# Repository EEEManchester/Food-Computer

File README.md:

# Food-Computer
A project to create a controlled indoor growing environment using embedded systems, sensors and control

Our plan is to build a www.eee.manchester.ac.uk  prototype version of the MIT OpenAgri "Food Computer" with an idea to scaling the design out in the future. 

####Please see our Github Wiki for all information on the project

Code and hardware are forked from https://github.com/OpenAgInitiative

For more information see here
https://www.media.mit.edu/special/groups/open-ag

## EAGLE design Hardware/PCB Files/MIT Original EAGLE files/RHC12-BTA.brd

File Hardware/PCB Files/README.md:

# gro-PCB
Robusto board, RHC12, and RHC12-BTA schematics/pcbs

Robusto is split into two parts, Part1 and Part2.  RHC12 is the base connector that works with Grove and 0.1" spaced header, RHC12-BTA is for a BTA connector.  

##THESE PCBS HAVE BEEN CONVERTED TO ALTIUM DESIGNER BY EEE MANCHESTER FROM EAGLE BOARD FILES CREATED AT MIT

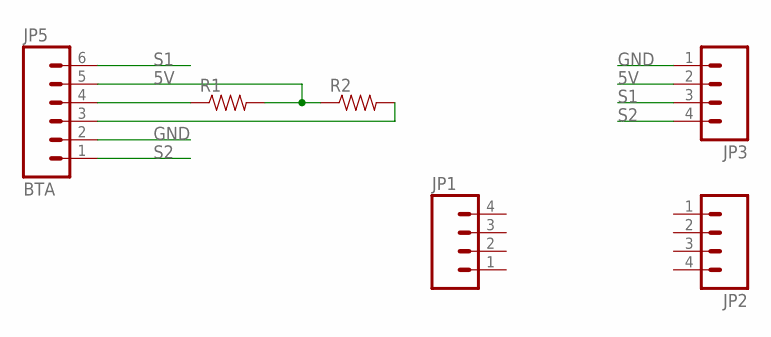
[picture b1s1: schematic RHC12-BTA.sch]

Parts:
JP1, JP2, JP3: M04NO_SILK_ALL_ROUND; 1X04_NO_SILK_ALL_ROUND
JP5: BTA
R1, R2: RESISTORPTH-1/4W; AXIAL-0.4

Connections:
5V: JP3.2, JP5.5, R1.P$2 (2), R2.P$1 (1)
GND: JP3.1, JP5.2
unnamed: JP5.4, R1.P$1 (1)
unnamed: JP5.3, R2.P$2 (2)
S1: JP3.3, JP5.6
S2: JP3.4, JP5.1

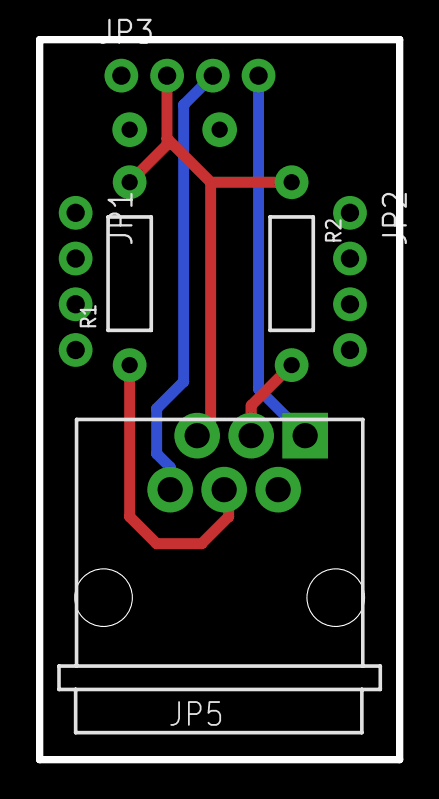
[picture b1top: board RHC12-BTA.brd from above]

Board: 2 copper layers, 20.0 x 40.0 mm, 6 parts (0 on the bottom side), 6 nets.

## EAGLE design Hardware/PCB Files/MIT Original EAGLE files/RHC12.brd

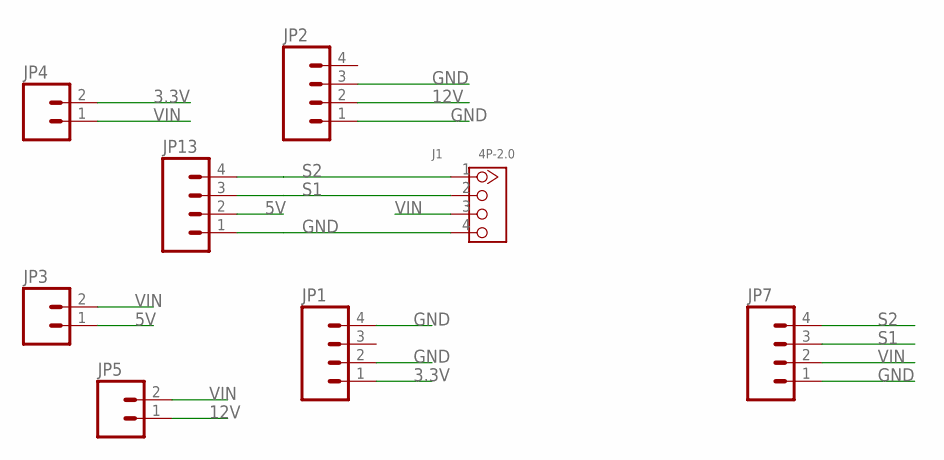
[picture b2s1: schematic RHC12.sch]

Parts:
J1: 4P-2.0; HW4-2.0
JP1, JP2, JP13: M04NO_SILK_ALL_ROUND; 1X04_NO_SILK_ALL_ROUND
JP3, JP4, JP5: M02PTH; 1X02
JP7: M04PTH; 1X04

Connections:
3.3V: JP1.1, JP4.2
5V: JP3.1, JP13.2
12V: JP2.2, JP5.1
GND: J1.4, JP1.2, JP1.4, JP2.1, JP2.3, JP7.1, JP13.1
S1: J1.2, JP7.3, JP13.3
S2: J1.1, JP7.4, JP13.4
VIN: J1.3, JP3.2, JP4.1, JP5.2, JP7.2

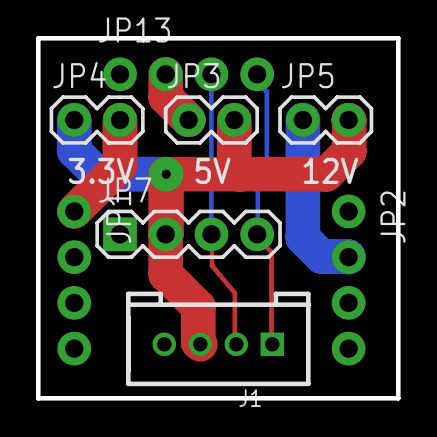
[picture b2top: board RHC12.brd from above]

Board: 2 copper layers, 20.0 x 20.0 mm, 8 parts (0 on the bottom side), 7 nets.

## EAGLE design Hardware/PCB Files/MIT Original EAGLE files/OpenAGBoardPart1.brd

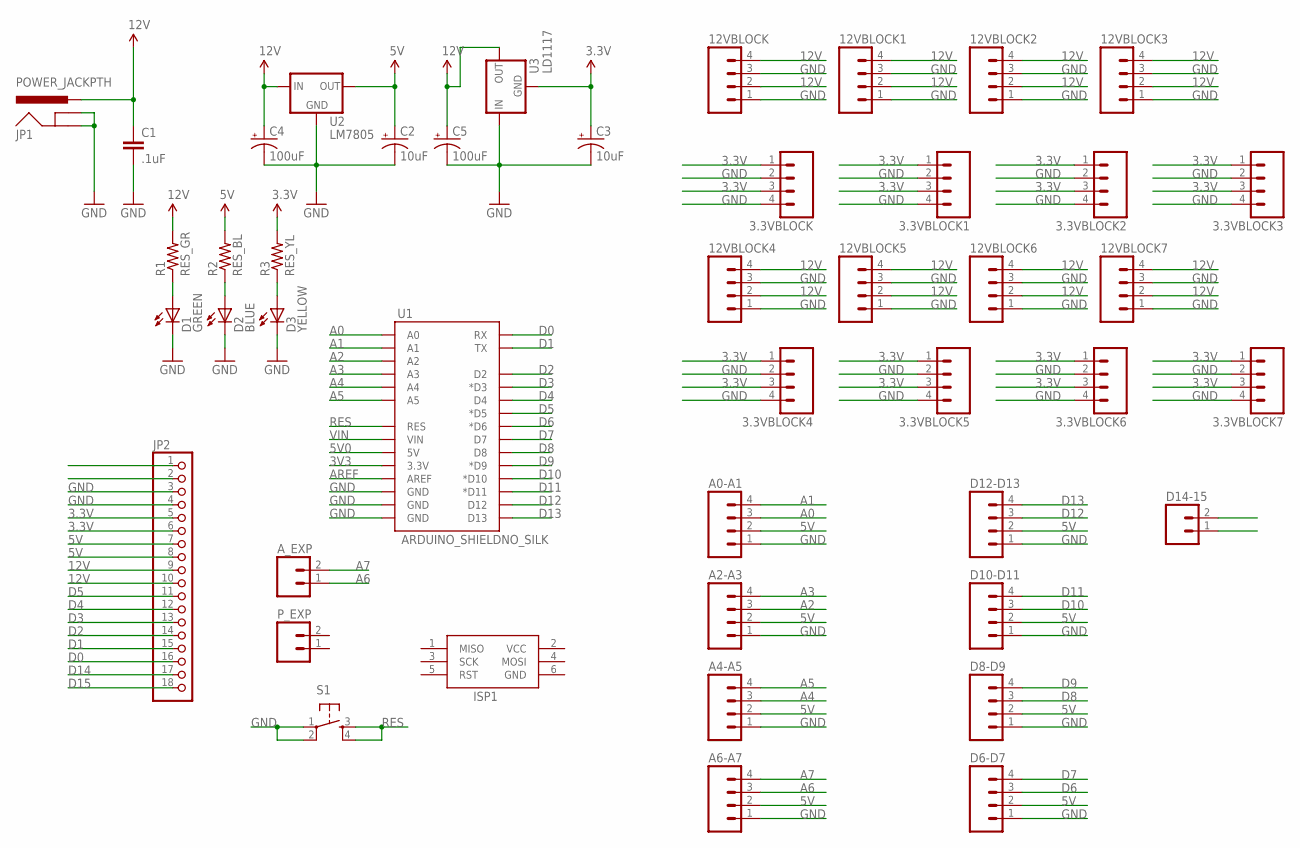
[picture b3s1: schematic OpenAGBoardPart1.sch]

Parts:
3.3VBLOCK, 3.3VBLOCK1, 3.3VBLOCK2, 3.3VBLOCK3, 3.3VBLOCK4, 3.3VBLOCK5, 3.3VBLOCK6, 3.3VBLOCK7, 12VBLOCK, 12VBLOCK1, 12VBLOCK2, 12VBLOCK3, 12VBLOCK4, 12VBLOCK5, 12VBLOCK6, 12VBLOCK7: M04NO_SILK_ALL_ROUND; 1X04_NO_SILK_ALL_ROUND
A0-A1, A2-A3, A4-A5, A6-A7: M04NO_SILK_ALL_ROUND; 1X04_NO_SILK_ALL_ROUND
A_EXP: M02PTH; 1X02
C1: .1uF; CAP-PTH-SMALL
C2, C3: 10uF; CPOL-RADIAL-10UF-25V
C4, C5: 100uF; CPOL-RADIAL-100UF-25V
D1: GREEN; LED5MM
D2: BLUE; LED5MM
D3: YELLOW; LED5MM
D6-D7, D8-D9, D10-D11, D12-D13: M04NO_SILK_ALL_ROUND; 1X04_NO_SILK_ALL_ROUND
D14-15: M02PTH; 1X02
ISP1: AVRISP-6; AVRISP
JP1: POWER_JACKPTH; POWER_JACK_PTH
JP2: PINHD-1X18-BIG; 1X18-BIG
P_EXP: M02PTH; 1X02
R1: RES_GR; AXIAL-0.4
R2: RES_BL; AXIAL-0.4
R3: RES_YL; AXIAL-0.4
S1: TAC_SWITCHPTH; TACTILE-PTH
U1: ARDUINO_SHIELDNO_SILK; DUEMILANOVE_VIAS
U2: LM7805; TO220-IGO
U3: LD1117; TO220-IGO

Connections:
3.3V: 3.3VBLOCK.1, 3.3VBLOCK.3, 3.3VBLOCK1.1, 3.3VBLOCK1.3, 3.3VBLOCK2.1, 3.3VBLOCK2.3, 3.3VBLOCK3.1, 3.3VBLOCK3.3, 3.3VBLOCK4.1, 3.3VBLOCK4.3, 3.3VBLOCK5.1, 3.3VBLOCK5.3, 3.3VBLOCK6.1, 3.3VBLOCK6.3, 3.3VBLOCK7.1, 3.3VBLOCK7.3, C3.1 (+), JP2.5, JP2.6, R3.P$2 (2), U3.GND
3V3: U1.3.3V
5V: A0-A1.2, A2-A3.2, A4-A5.2, A6-A7.2, C2.1 (+), D6-D7.2, D8-D9.2, D10-D11.2, D12-D13.2, JP2.7, JP2.8, R2.P$2 (2), U2.OUT
5V0: U1.5V
12V: 12VBLOCK.2, 12VBLOCK.4, 12VBLOCK1.2, 12VBLOCK1.4, 12VBLOCK2.2, 12VBLOCK2.4, 12VBLOCK3.2, 12VBLOCK3.4, 12VBLOCK4.2, 12VBLOCK4.4, 12VBLOCK5.2, 12VBLOCK5.4, 12VBLOCK6.2, 12VBLOCK6.4, 12VBLOCK7.2, 12VBLOCK7.4, C1.1, C4.1 (+), C5.1 (+), JP1.PWR, JP2.9, JP2.10, R1.P$2 (2), U2.IN, U3.OUT
A0: A0-A1.3, U1.A0
A1: A0-A1.4, U1.A1
A2: A2-A3.3, U1.A2
A3: A2-A3.4, U1.A3
A4: A4-A5.3, U1.A4
A5: A4-A5.4, U1.A5
A6: A6-A7.3, A_EXP.1
A7: A6-A7.4, A_EXP.2
AREF: U1.AREF
CONTINUITY_STRIP: JP2.1
D0: JP2.16, U1.RX
D1: JP2.15, U1.TX
D2: JP2.14, U1.D2
D3: JP2.13, U1.D3 (*D3)
D4: JP2.12, U1.D4
D5: JP2.11, U1.D5 (*D5)
D6: D6-D7.3, U1.D6 (*D6)
D7: D6-D7.4, U1.D7
D8: D8-D9.3, U1.D8
D9: D8-D9.4, U1.D9 (*D9)
D10: D10-D11.3, U1.D10 (*D10)
D11: D10-D11.4, U1.D11 (*D11)
D12: D12-D13.3, U1.D12
D13: D12-D13.4, U1.D13
D14: D14-15.1, JP2.17
D15: D14-15.2, JP2.18
GND: 3.3VBLOCK.2, 3.3VBLOCK.4, 3.3VBLOCK1.2, 3.3VBLOCK1.4, 3.3VBLOCK2.2, 3.3VBLOCK2.4, 3.3VBLOCK3.2, 3.3VBLOCK3.4, 3.3VBLOCK4.2, 3.3VBLOCK4.4, 3.3VBLOCK5.2, 3.3VBLOCK5.4, 3.3VBLOCK6.2, 3.3VBLOCK6.4, 3.3VBLOCK7.2, 3.3VBLOCK7.4, 12VBLOCK.1, 12VBLOCK.3, 12VBLOCK1.1, 12VBLOCK1.3, 12VBLOCK2.1, 12VBLOCK2.3, 12VBLOCK3.1, 12VBLOCK3.3, 12VBLOCK4.1, 12VBLOCK4.3, 12VBLOCK5.1, 12VBLOCK5.3, 12VBLOCK6.1, 12VBLOCK6.3, 12VBLOCK7.1, 12VBLOCK7.3, A0-A1.1, A2-A3.1, A4-A5.1, A6-A7.1, C1.2, C2.2 (-), C3.2 (-), C4.2 (-), C5.2 (-), D1.K (C), D2.K (C), D3.K (C), D6-D7.1, D8-D9.1, D10-D11.1, D12-D13.1, ISP1.6 (GND), JP1.GND, JP1.GNDBREAK, JP2.3, JP2.4, S1.1, S1.2, U1.GND@0 (GND), U1.GND@1 (GND), U1.GND@2 (GND), U2.GND, U3.IN
unnamed: D1.A, R1.P$1 (1)
unnamed: D2.A, R2.P$1 (1)
unnamed: D3.A, R3.P$1 (1)
RES: S1.3, S1.4, U1.RES
VCC: ISP1.2 (VCC)
VIN: U1.VIN

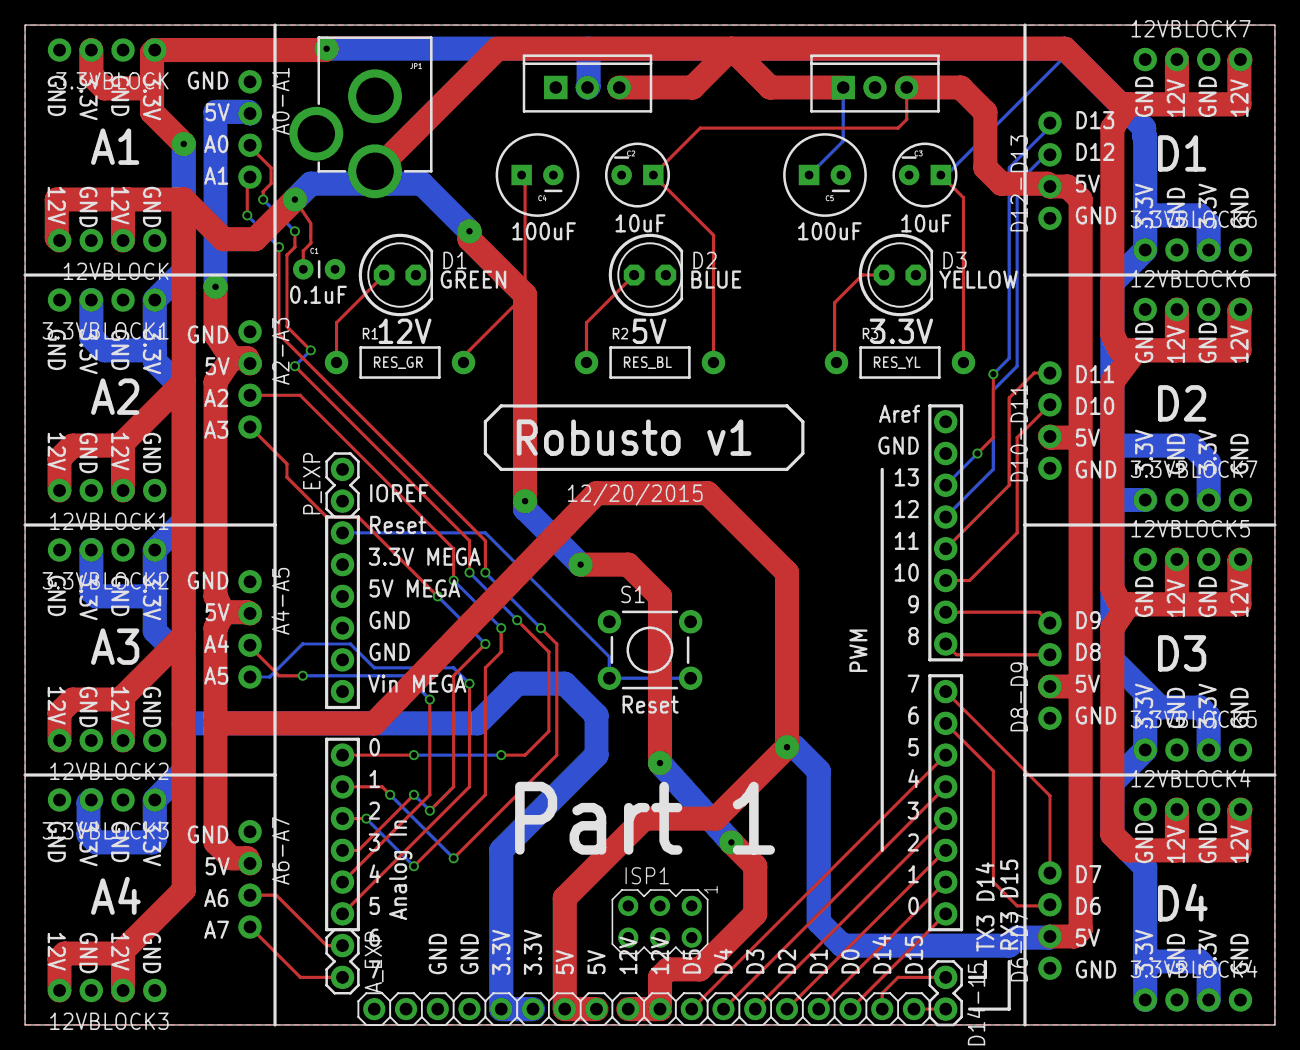
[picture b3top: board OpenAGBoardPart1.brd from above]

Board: 2 copper layers, 100.0 x 80.0 mm, 45 parts (0 on the bottom side), 32 nets.

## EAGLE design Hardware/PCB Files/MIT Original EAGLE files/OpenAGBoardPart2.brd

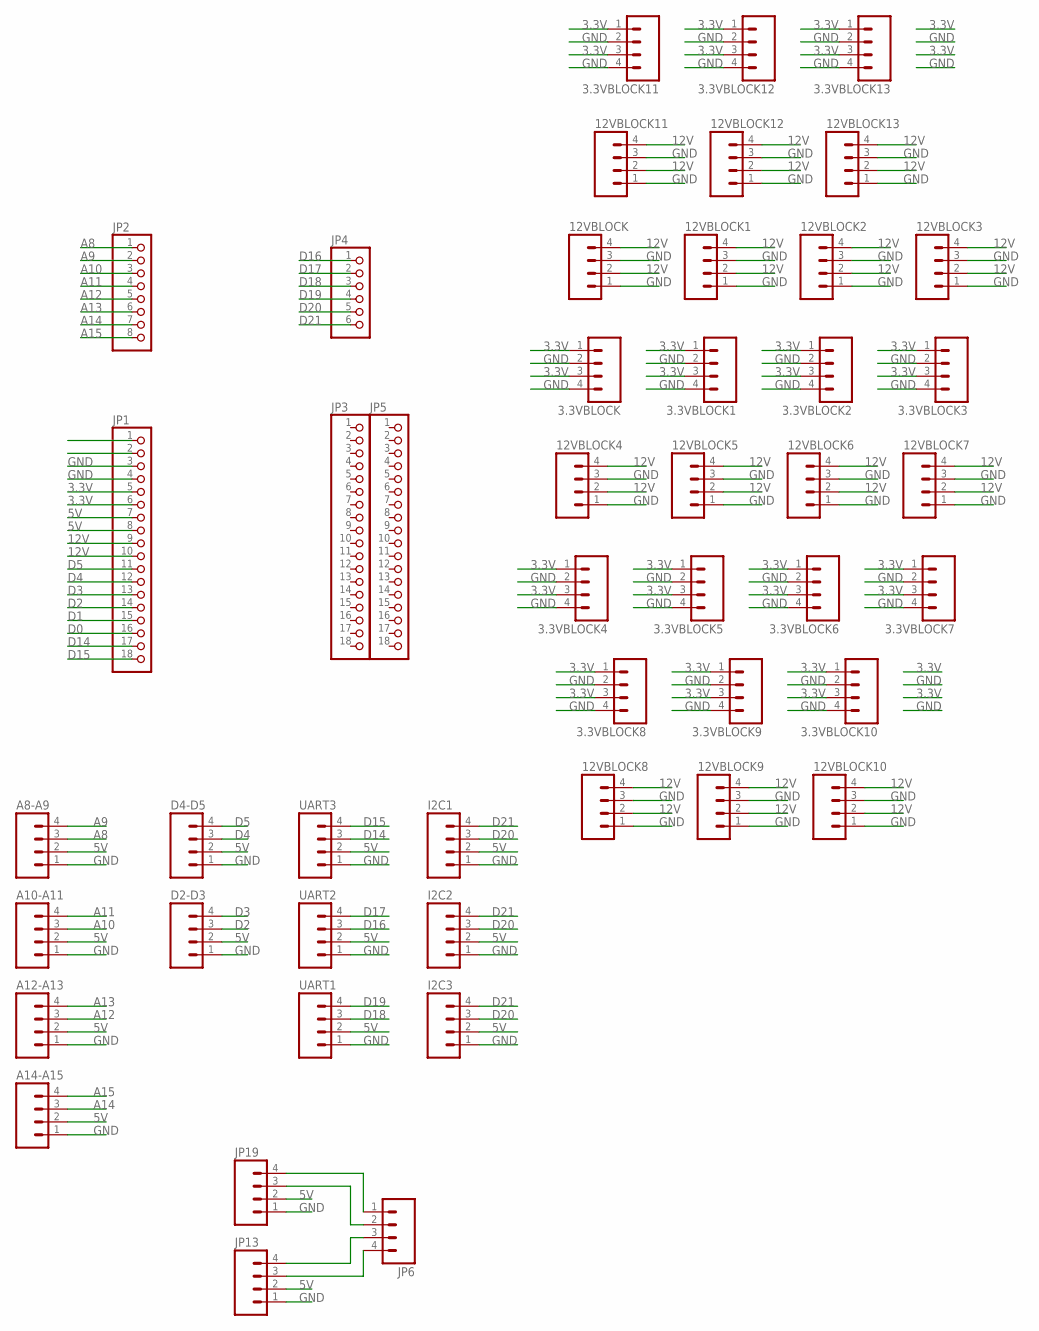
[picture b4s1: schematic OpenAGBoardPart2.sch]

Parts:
3.3VBLOCK, 3.3VBLOCK1, 3.3VBLOCK2, 3.3VBLOCK3, 3.3VBLOCK4, 3.3VBLOCK5, 3.3VBLOCK6, 3.3VBLOCK7, 3.3VBLOCK8, 3.3VBLOCK9, 3.3VBLOCK10, 3.3VBLOCK11, 3.3VBLOCK12, 3.3VBLOCK13, 12VBLOCK, 12VBLOCK1, 12VBLOCK2, 12VBLOCK3, 12VBLOCK4, 12VBLOCK5, 12VBLOCK6, 12VBLOCK7, 12VBLOCK8, 12VBLOCK9, 12VBLOCK10, 12VBLOCK11, 12VBLOCK12, 12VBLOCK13: M04NO_SILK_ALL_ROUND; 1X04_NO_SILK_ALL_ROUND
A8-A9, A10-A11, A12-A13, A14-A15: M04NO_SILK_ALL_ROUND; 1X04_NO_SILK_ALL_ROUND
D2-D3, D4-D5: M04NO_SILK_ALL_ROUND; 1X04_NO_SILK_ALL_ROUND
I2C1, I2C2, I2C3: M04NO_SILK_ALL_ROUND; 1X04_NO_SILK_ALL_ROUND
JP1, JP3, JP5: PINHD-1X18-BIG; 1X18-BIG
JP2: PINHD-1X8BIG; 1X08-BIG
JP4: PINHD-1X6B; 1X06-BIG
JP6: M04PTH; 1X04
JP13, JP19: M04NO_SILK_ALL_ROUND; 1X04_NO_SILK_ALL_ROUND
UART1, UART2, UART3: M04NO_SILK_ALL_ROUND; 1X04_NO_SILK_ALL_ROUND

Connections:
3.3V: 3.3VBLOCK.1, 3.3VBLOCK.3, 3.3VBLOCK1.1, 3.3VBLOCK1.3, 3.3VBLOCK2.1, 3.3VBLOCK2.3, 3.3VBLOCK3.1, 3.3VBLOCK3.3, 3.3VBLOCK4.1, 3.3VBLOCK4.3, 3.3VBLOCK5.1, 3.3VBLOCK5.3, 3.3VBLOCK6.1, 3.3VBLOCK6.3, 3.3VBLOCK7.1, 3.3VBLOCK7.3, 3.3VBLOCK8.1, 3.3VBLOCK8.3, 3.3VBLOCK9.1, 3.3VBLOCK9.3, 3.3VBLOCK10.1, 3.3VBLOCK10.3, 3.3VBLOCK11.1, 3.3VBLOCK11.3, 3.3VBLOCK12.1, 3.3VBLOCK12.3, 3.3VBLOCK13.1, 3.3VBLOCK13.3, JP1.5, JP1.6
5V: A8-A9.2, A10-A11.2, A12-A13.2, A14-A15.2, D2-D3.2, D4-D5.2, I2C1.2, I2C2.2, I2C3.2, JP1.7, JP1.8, JP13.2, JP19.2, UART1.2, UART2.2, UART3.2
12V: 12VBLOCK.2, 12VBLOCK.4, 12VBLOCK1.2, 12VBLOCK1.4, 12VBLOCK2.2, 12VBLOCK2.4, 12VBLOCK3.2, 12VBLOCK3.4, 12VBLOCK4.2, 12VBLOCK4.4, 12VBLOCK5.2, 12VBLOCK5.4, 12VBLOCK6.2, 12VBLOCK6.4, 12VBLOCK7.2, 12VBLOCK7.4, 12VBLOCK8.2, 12VBLOCK8.4, 12VBLOCK9.2, 12VBLOCK9.4, 12VBLOCK10.2, 12VBLOCK10.4, 12VBLOCK11.2, 12VBLOCK11.4, 12VBLOCK12.2, 12VBLOCK12.4, 12VBLOCK13.2, 12VBLOCK13.4, JP1.9, JP1.10
A8: A8-A9.3, JP2.1
A9: A8-A9.4, JP2.2
A10: A10-A11.3, JP2.3
A11: A10-A11.4, JP2.4
A12: A12-A13.3, JP2.5
A13: A12-A13.4, JP2.6
A14: A14-A15.3, JP2.7
A15: A14-A15.4, JP2.8
D0: JP1.16
D1: JP1.15
D2: D2-D3.3, JP1.14
D3: D2-D3.4, JP1.13
D4: D4-D5.3, JP1.12
D5: D4-D5.4, JP1.11
D14: JP1.17, UART3.3
D15: JP1.18, UART3.4
D16: JP4.1, UART2.3
D17: JP4.2, UART2.4
D18: JP4.3, UART1.3
D19: JP4.4, UART1.4
D20: I2C1.3, I2C2.3, I2C3.3, JP4.5
D21: I2C1.4, I2C2.4, I2C3.4, JP4.6
GND: 3.3VBLOCK.2, 3.3VBLOCK.4, 3.3VBLOCK1.2, 3.3VBLOCK1.4, 3.3VBLOCK2.2, 3.3VBLOCK2.4, 3.3VBLOCK3.2, 3.3VBLOCK3.4, 3.3VBLOCK4.2, 3.3VBLOCK4.4, 3.3VBLOCK5.2, 3.3VBLOCK5.4, 3.3VBLOCK6.2, 3.3VBLOCK6.4, 3.3VBLOCK7.2, 3.3VBLOCK7.4, 3.3VBLOCK8.2, 3.3VBLOCK8.4, 3.3VBLOCK9.2, 3.3VBLOCK9.4, 3.3VBLOCK10.2, 3.3VBLOCK10.4, 3.3VBLOCK11.2, 3.3VBLOCK11.4, 3.3VBLOCK12.2, 3.3VBLOCK12.4, 3.3VBLOCK13.2, 3.3VBLOCK13.4, 12VBLOCK.1, 12VBLOCK.3, 12VBLOCK1.1, 12VBLOCK1.3, 12VBLOCK2.1, 12VBLOCK2.3, 12VBLOCK3.1, 12VBLOCK3.3, 12VBLOCK4.1, 12VBLOCK4.3, 12VBLOCK5.1, 12VBLOCK5.3, 12VBLOCK6.1, 12VBLOCK6.3, 12VBLOCK7.1, 12VBLOCK7.3, 12VBLOCK8.1, 12VBLOCK8.3, 12VBLOCK9.1, 12VBLOCK9.3, 12VBLOCK10.1, 12VBLOCK10.3, 12VBLOCK11.1, 12VBLOCK11.3, 12VBLOCK12.1, 12VBLOCK12.3, 12VBLOCK13.1, 12VBLOCK13.3, A8-A9.1, A10-A11.1, A12-A13.1, A14-A15.1, D2-D3.1, D4-D5.1, I2C1.1, I2C2.1, I2C3.1, JP1.3, JP1.4, JP13.1, JP19.1, UART1.1, UART2.1, UART3.1
unnamed: JP6.1, JP19.4
unnamed: JP6.2, JP19.3
unnamed: JP6.3, JP13.4
unnamed: JP6.4, JP13.3

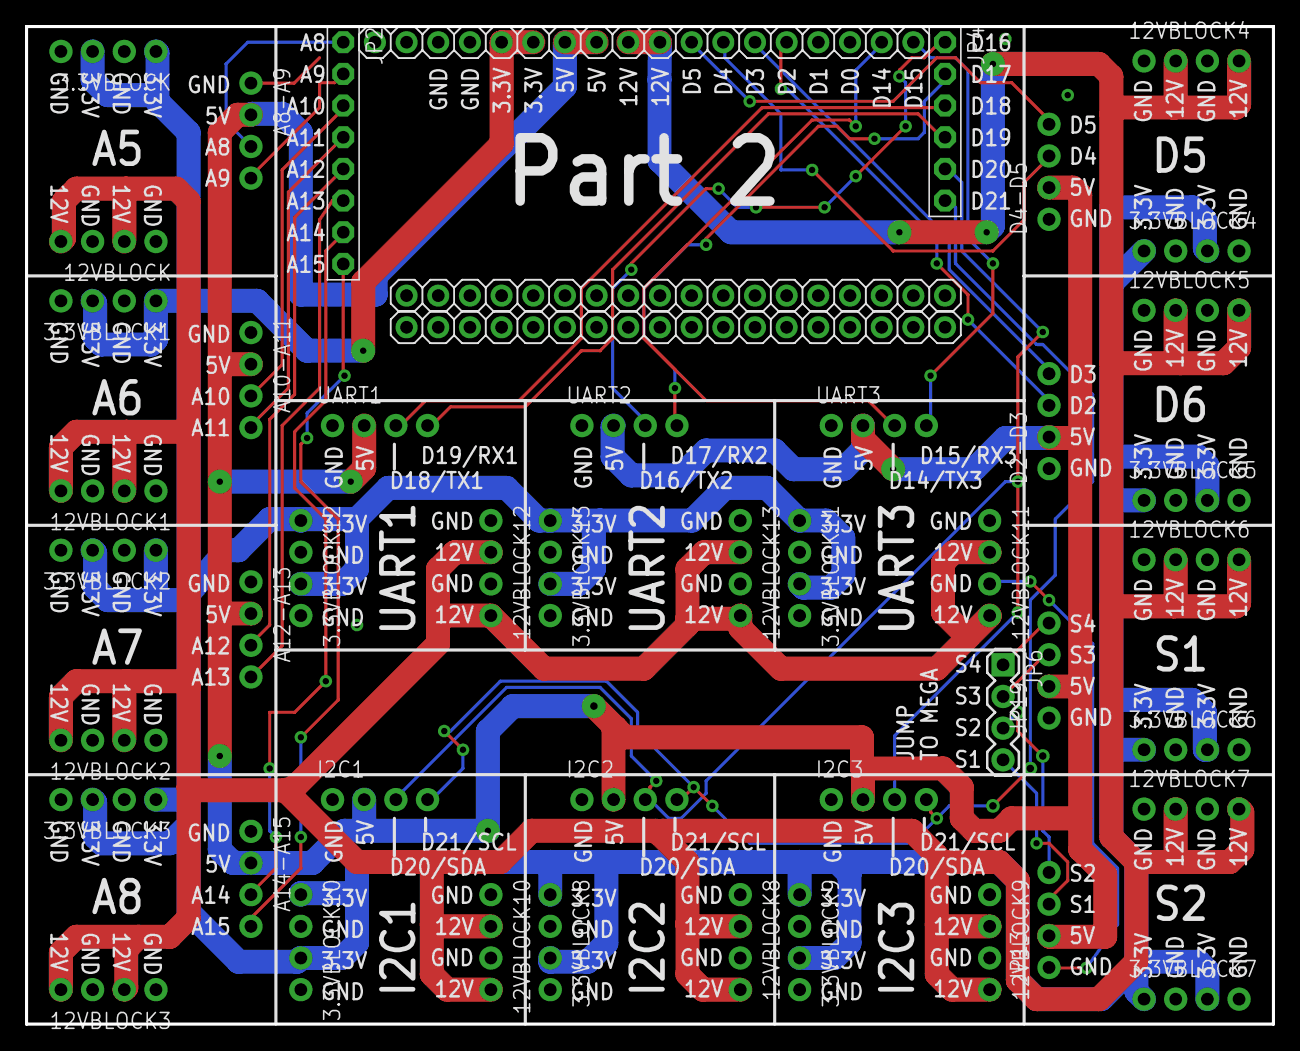
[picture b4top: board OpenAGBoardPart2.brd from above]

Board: 2 copper layers, 100.0 x 80.0 mm, 48 parts (0 on the bottom side), 28 nets.

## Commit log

2016-05-19 Added hardware and UK suppliers
2016-05-19 added PCB and microcontroller software
    this needs going through to make sure it is up to date
2016-05-19 Converted PCB files to Altium
2016-05-19 added food computer photo
2016-05-19 added photos of PCBs and converted to Altium Smart PDF
2016-06-15 first upload test
2016-06-15 deleted first upload test
2016-06-16 added schematic for protoshield from http://adrianllu.com/category/food-computer/
2016-06-16 (updated to hi-res) added schematic for protoshield from http://adrianllu.com/category/food-computer/
2016-06-23 Added SimpleIO, a draft used for simple GUI test. Not optimised yet.
2016-07-04 added Food_Computer_Draft_V2
2016-07-04 Library issue fixed (Wire.h).
2016-07-18 Added simple MQTT GUI.
2016-07-28 Added ARM with MODBUS (mbed).
2016-08-08 added node-red flow V1
2016-09-15 added simple documentation (incomplete).
2016-09-15 please add 5 seconds delay if rasPi is stuck upon startup.

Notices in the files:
parts and their libraries:
SparkFun-Connectors: Licensing: Creative Commons ShareAlike 4.0 International - https://creativecommons.org/licenses/by-sa/4.0
SparkFun-Connectors: Licensing: CC v3.0 Share-Alike You are welcome to use this library for commercial purposes.
